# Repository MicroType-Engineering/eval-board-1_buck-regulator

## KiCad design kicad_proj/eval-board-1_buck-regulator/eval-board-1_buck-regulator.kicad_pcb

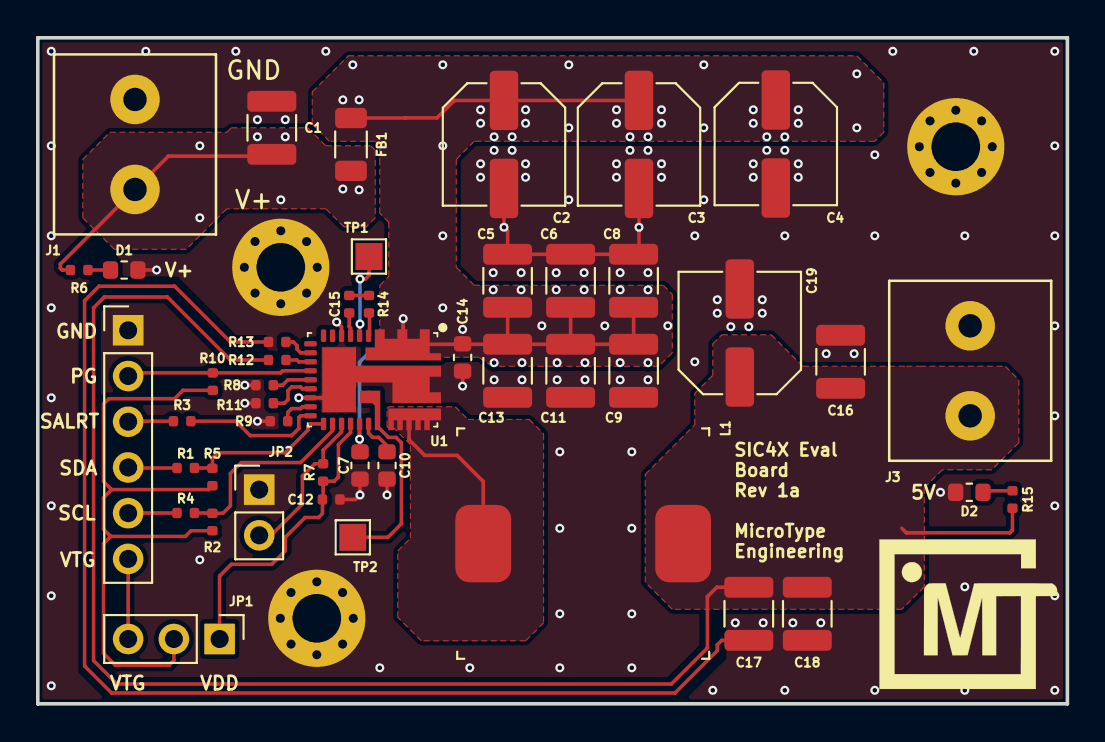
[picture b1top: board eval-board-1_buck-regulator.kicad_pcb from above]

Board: 4 copper layers, 57.2 x 37.0 mm, 49 parts (0 on the bottom side), 29 nets.

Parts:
C1, C16, C17, C18: GRM32ER71C226KEA8; CAPACITOR_1210N
C2, C3, C4, C19: UCH1V470MCS1GS; CAPAE660X580L260X65N
C5, C6, C8, C9, C11, C13: GRM32ER71E226ME15K; CAPACITOR_1210N
C7, C14: GRM188R61H225ME11D; CAPACITOR_0603N
C10: 4.7u; CAPACITOR_0603N
C12: 1u; CAPACITOR_0402N
C15: 0.1uF; CAPACITOR_0402N
D1, D2: LED; CAPACITOR_0603N
FB1: 74279221100; CAPACITOR_1206N
H1, H2, H3: MountingHole_Pad; MountingHole_2.7mm_M2.5_Pad_Via
J1, J3: Conn_01x02; 1935776
J2: Conn_01x06; PinHeader_1x06_P2.54mm_Vertical
JP1: Jumper_NC_Dual; PinHeader_1x03_P2.54mm_Vertical
JP2: Jumper; PinHeader_1x02_P2.54mm_Vertical
L1: PA4343.102NLT; PA4343_PM4343
R1, R3, R4, R15: 220; CAPACITOR_0402N
R2, R5, R7, R10, R12, R13: 10K; CAPACITOR_0402N
R6: 510; CAPACITOR_0402N
R8, R9, R11: 8.87K; CAPACITOR_0402N
R14: 2.2; CAPACITOR_0402N
TP1, TP2: TestPoint; TestPoint_Pad_1.5x1.5mm
U1: SIC453ED-T1-GE3; SiC45X

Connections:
+5V: C16.1, C17.1, C18.1, C19.1, J3.2, L1.2, R12.2, R15.1
+12V: C1.1, FB1.1, J1.2, R6.1
/EN: JP2.2, R7.2, U1.21 (EN)
/EXTERN_VTG: J2.6, JP1.3
/PGOOD: J2.2, R10.2, U1.13 (PGOOD)
/PULLUP_VTG: JP1.2, R2.1, R5.1, R10.1
/SALERT: R3.2, U1.18 (SALRT)
/SCL: R2.2, R4.2, U1.20 (SCL)
/SDA: R1.2, R5.2, U1.19 (SDA)
/VDD: C12.1, JP1.1, R7.1, U1.22 (VDD)
GND: C1.2, C2.2, C3.2, C4.2, C5.2, C6.2, C7.2, C8.2, C9.2, C10.2, C11.2, C12.2, C13.2, C14.2, C16.2, C17.2, C18.2, C19.2, D1.1 (K), D2.1 (K), H1.1, H2.1, H3.1, J1.1, J2.1, J3.1, JP2.1, R8.2, R9.2, R11.2, R13.2, U1.7 (AGND), U1.16 (AGND), U1.32 (PGND)
unnamed: C10.1, U1.24 (PVCC)
unnamed: C2.1, C3.1, C4.1, C5.1, C6.1, C7.1, C8.1, C9.1, C11.1, C13.1, C14.1, FB1.2, U1.1 (PVIN), U1.23 (VIN)
unnamed: C15.1, U1.6 (BOOT)
unnamed: C15.2, R14.1
unnamed: D1.2 (A), R6.2
unnamed: D2.2 (A), R15.2
unnamed: J2.3, R3.1
unnamed: J2.4, R1.1
unnamed: J2.5, R4.1
unnamed: L1.1, U1.26 (SW)
unnamed: R8.1, U1.14 (ADDR)
unnamed: R9.1, U1.17 (RT/SYNC)
unnamed: R11.1, U1.15 (VSET)
unnamed: R12.1, U1.12 (VSEN+)
unnamed: R13.1, U1.11 (VSEN-)
unnamed: R14.2, U1.4 (PH)
unnamed: TP1.1, U1.5 (GH)
unnamed: TP2.1, U1.25 (GL)

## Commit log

2021-07-31 Sets up project
2021-07-31 Updates from the first stream
2021-08-07 Updates from livestream
2021-08-21 Livestream updates
2021-09-08 Updates gitignore to exclude .zip files
2021-09-08 Updates silkscreen to board
2021-09-09 Add fill keepout for analog lines, 12v led trace, slight adjust to fills
2021-09-09 Added vias around caps
2021-09-09 Added general stitching vias
2021-09-09 Minor adjust to refdes for clarity, add labels to leds
2021-10-21 Adds license to repo
